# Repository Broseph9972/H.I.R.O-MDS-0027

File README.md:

# H.I.R.O-MDS-0027
a music video faithful mp3 player based on the H.I.R.O from good kid Music videos. built for Hack club fallout in about 2 weeks. My favorite Hardware project yet
---

I unironically listened to almost exclusively good kid while making this project.

---
## Why?
I've always loved good kid, and i was bored at night watching some of their music videos, and saw a scene of the H.I.R.O taken apart with a soldering iron,[^1] and realised, i could probably make that.
I cant explain how to use it yet, as i have not built it yet, but it should go something like select a song or playlist, and itll play said song or playlist. (duh)
This is my first project where i'm not very concerned about budget, as it isnt completely practical, it just needs to look as close as possible to the original. I did get rid of the arms and legs because it would make it annoying to use imho.

# Assembly

## Read through this before starting just for understanding.

  1. Solder Parts Onto the PCB. As there are many SMD Components and small capacitors, reflow soldering is recommended. Use long header pins for the screen DO NOT SOLDER THE SCREEN TO THE PCB YET.
  2. If any Through Hole parts poke into the case, like the speaker, use pliers or something to take them off. there should be indents in the case for them though.
  3. Place the PCB Onto the Main Casing. If it dosent fit, just sand the part until it does.
  4. Screw In the screen to the 4 square brackets on the main casing with M3x14 Screws.
  5. Solder the Screen Connector pins to the screen. (if gpio are short, im so sorry but i would just desolder and use jumper wires.)
  6. Plug in the battery to the JST Connector. Slide it wherever it fits, i reccomend under the screen. any lipo battery should work.
  7. (vid isnt accurate) Slide the buttons into place so that the lip dosent allow it to get pushed out.
  8. Place the Lid on Top, Turn the main casing over, and screw in 3 M3x14 Screws.
  9. (Optional) Paint it! it looks so much cooler Painted. I highly reccomend this.

### Assembly Video (its really bad)
https://github.com/user-attachments/assets/d8cce7da-2541-4a06-ba8f-5a0993665533

# Usage
The H.I.R.O has 3 inputs.
1. Button 1
2. Button 2
3. Clicky Knob

Spin the knob to cycle through the options on the screen. Click the knob to select.
Button 1 is for skipping to the next song. Hold to skip past 10s at a time in a specific song.
Button 2 is for rewinding. Click once to go to the last song. click twice to restart the song. Hold to go back 10s at a time in the song. 
# Setup
  1. Flash the Firmware for the MP3 Using arduino IDE or whichever ide you prefer
  2. Insert MicroSD Card With Music on it in Mp3 (or FLAC?) Format.
  3. Play your Music!

## Warning:
Theres a bug where the lid has a huge object inside it when 3d printing, just delete it in your slicer. i dunno why this happens.

# Bill of Materials

| Name | Qty | Reference(s) | Price (USD) | Comments | Link |
|------|-----|--------------|-------------|----------|------|
| Seeed XIAO ESP32-S3 Plus | 1 | U1 | $7.59 | Main MCU module. SMD footprint (castellated). Source direct from Seeed for genuine part. | [Link](https://www.seeedstudio.com/Seeed-Studio-XIAO-ESP32S3-Plus-p-6361.html) |
| PCM5102A DAC (TSSOP-20) | 1 | U2 | $1.11 | Bare IC from LCSC (C107671). I2S DAC driving the 3.5mm headphone jack. | [Link](https://www.lcsc.com/product-detail/C107671.html) |
| MAX98357A Class-D Amplifier (TQFN-16) | 1 | U3 | $2.00 | Bare TQFN-16 3x3mm IC — NOT a breakout module. Check LCSC / DigiKey / Mouser for current price. | [Link](https://octopart.com/max98357aete+t-maxim+integrated-33346832) |
| CVS-1708 Speaker | 1 | LS1 | $4.02 | 8Ω 200mW 1.2kHz–20kHz. Same Sky (formerly CUI). DigiKey. | [Link](https://www.digikey.com/en/products/detail/same-sky-formerly-cui-devices/CVS-1708/2791829) |
| Hirose DM3AT-SF-PEJM5 microSD Slot | 1 | J1 | $1.53 | Push-push with card detect. LCSC (C114218). | [Link](https://www.lcsc.com/product-detail/SD-Card-Connectors_HRS-Hirose-DM3AT-SF-PEJM5_C114218.html) |
| CUI SJ-3523-SMT-TR 3.5mm Audio Jack | 1 | J2 | $0.88 | Horizontal SMT stereo TRS jack. DigiKey. | [Link](https://www.digikey.com/en/products/detail/cui-devices/SJ-3523-SMT-TR/281297) |
| 1×8 Pin Header 2.54mm (through-hole) | 1 | J3 | $7.99 | Screen connector for Waveshare LCD. Must use long header pins (see assembly notes). | [Link](https://www.amazon.com/whiteeeen-Break-Away-Header-Straight-Connector/dp/B0B75RKMD2) |
| JST PH S2B-PH-K 2-pin Connector | 1 | J4 | $0.11 | Battery connector. 2.0mm pitch horizontal SMT. | [Link](https://www.digikey.com/en/products/detail/jst-sales-america-inc/S2B-PH-K-S/926626) |
| Omron B3U-3100P-B Side Push Button | 2 | S1 / S2 | $1.17 | SMD side-actuated tactile. DigiKey. ×2 units needed. | [Link](https://www.digikey.com/en/products/detail/omron-electronics-inc-emc-div/B3U-3100P-B/1811780) |
| EC11 Right-Angle Rotary Encoder (w/ switch) | 1 | SW1 | $4.07 | Push-switch + encoder. Right-angle EC11. | [Link](https://www.aliexpress.us/item/3256809185234399.html) |
| Capacitor 10µF 0603 | 4 | C1 / C4 / C5 / C6 | $0.01 | X5R or X7R ceramic decoupling. Order from LCSC. | [Link](https://www.lcsc.com/search?q=10uF+0603) |
| Capacitor 100nF 0603 | 2 | C2 / C3 | $0.01 | X7R ceramic decoupling. Order from LCSC. | [Link](https://www.lcsc.com/search?q=100nF+0603) |
| Resistor 1MΩ 0603 | 1 | R1 | $0.01 | 1% tolerance preferred. Order from LCSC. | [Link](https://www.lcsc.com/search?q=1M+0603+resistor) |
| Waveshare 2.4in LCD Module | 1 | — | $18.99 | 240×320 SPI (ILI9341). Connects to J3 header. Closest size match to original H.I.R.O screen. | [Link](https://www.amazon.com/Waveshare-2-4inch-Display-Resolution-Interface/dp/B08H24H7KX) |
| LiPo Battery 3.7V | 1 | — | $9.99 | Any single-cell LiPo with JST PH 2.0mm connector. Slides under screen in case. 500mAh+ recommended. | [Link](https://www.amazon.com/Battery-Rechargeable-Lithium-Polymer-Connector/dp/B07S84SBV3) |
| M3×14 Socket Head Cap Screws | 7 | — | $6.99 | 4× screen brackets + 3× lid. Stainless steel A2. | [Link](https://a.co/d/00dNH8NP) |
| 3D Printed Main Casing | 1 | — | $0.10 | Print from Cad/ directory. Sand if needed for PCB fit (see assembly notes). | [Link](https://github.com/Broseph9972/H.I.R.O-MDS-0027/tree/main/Cad) |
| 3D Printed Lid | 1 | — | $0.10 | Print from Cad/ directory. 3× M3×14 screw holes. | [Link](https://github.com/Broseph9972/H.I.R.O-MDS-0027/tree/main/Cad) |
| Custom PCB (H.I.R.O) | 1 | — | $7.50 | Fabricate from Pcb/ gerbers. JLCPCB / PCBWay / OSH Park. | [Link](https://github.com/Broseph9972/H.I.R.O-MDS-0027/tree/main/Pcb) |
| Paint (optional) | 1 | — | $0 | Spray paint or acrylic. | — |
| **TOTAL** | — | — | **$75.38** | Qty × unit price across all lines (screws/header counted as pack price; optional paint at $0). | — |

[^1]:From [Eastside](https://www.youtube.com/watch?v=-kVTMlbAywQ) [Wall](https://www.youtube.com/watch?v=HG8WEN3SKVk)[Mimis Delivery Service](https://www.youtube.com/watch?v=hYUvI5Njbbk)

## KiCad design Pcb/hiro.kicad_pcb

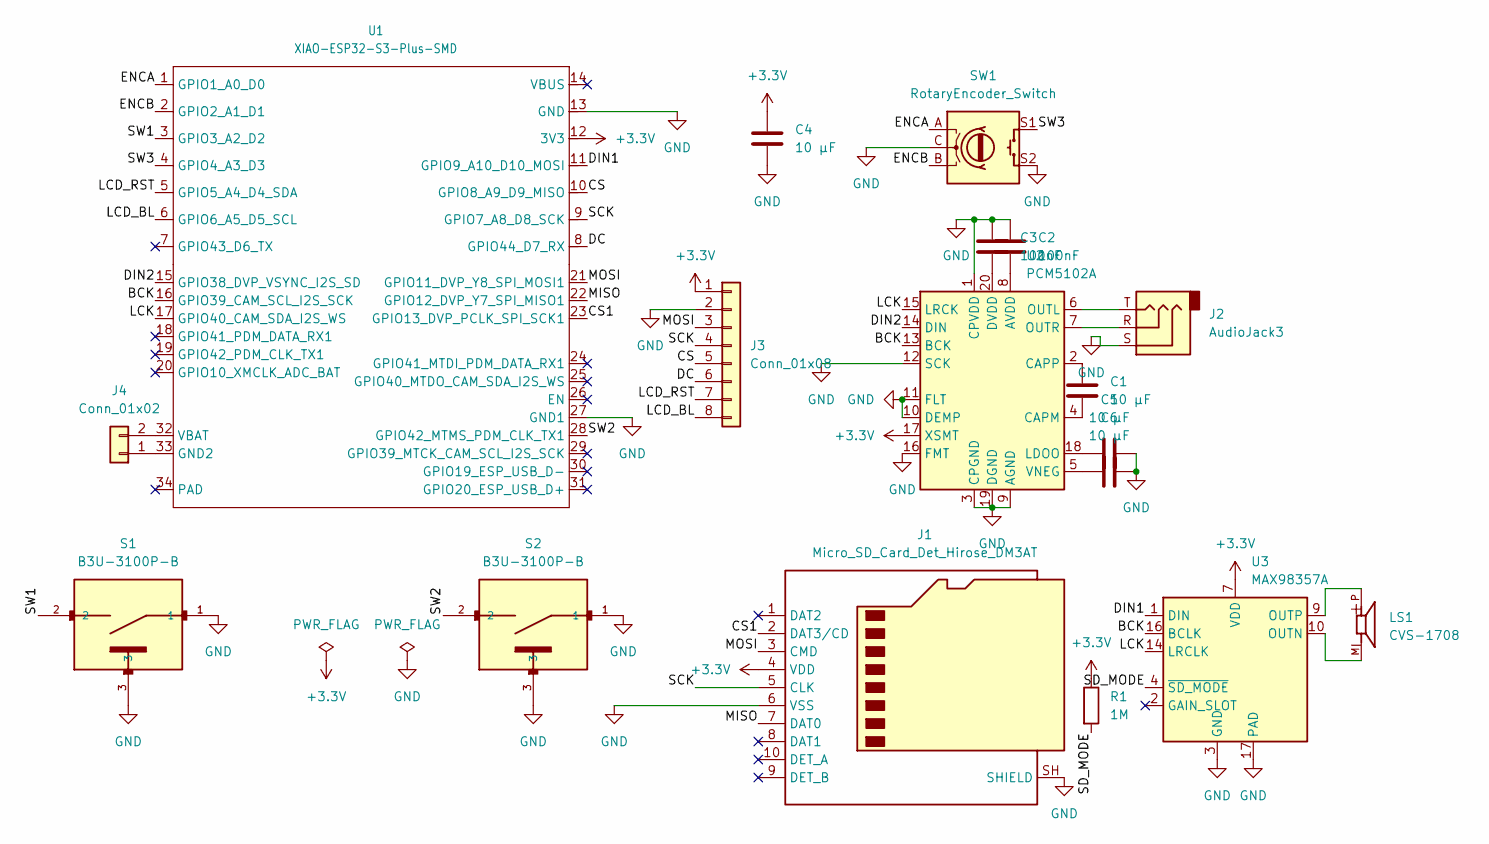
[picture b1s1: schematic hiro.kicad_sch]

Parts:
C1, C4, C5, C6: 10 µF; C_0603_1608Metric_Pad1.08x0.95mm_HandSolder
C2, C3: 100nF; C_0603_1608Metric_Pad1.08x0.95mm_HandSolder
J1: Micro_SD_Card_Det_Hirose_DM3AT; microSD_HC_Hirose_DM3AT-SF-PEJM5
J2: AudioJack3; Jack_3.5mm_CUI_SJ-3523-SMT_Horizontal
J3: Conn_01x08; PinHeader_1x08_P2.54mm_Vertical
J4: Conn_01x02; JST_PH_S2B-PH-K_1x02_P2.00mm_Horizontal
LS1: CVS-1708; SPKR_CVS-1708
R1: 1M; R_0603_1608Metric_Pad0.98x0.95mm_HandSolder
S1, S2: B3U-3100P-B; SW_SPST_B3U-3100P
SW1: RotaryEncoder_Switch; Right angle EC11 Rotary Encoder
U1: XIAO-ESP32-S3-Plus-SMD
U2: PCM5102A; TSSOP-20_4.4x6.5mm_P0.65mm
U3: MAX98357A; TQFN-16-1EP_3x3mm_P0.5mm_EP1.23x1.23mm

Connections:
+3.3V: C4.1, J1.4 (VDD), J3.1, R1.1, U1.12 (3V3), U2.17 (XSMT), U3.7 (VDD), U3.8 (VDD)
/BCK: U1.16 (GPIO39_CAM_SCL_I2S_SCK), U2.13 (BCK), U3.16 (BCLK)
/CS: J3.5, U1.10 (GPIO8_A9_D9_MISO)
/CS1: J1.2 (DAT3/CD), U1.23 (GPIO13_DVP_PCLK_SPI_SCK1)
/DC: J3.6, U1.8 (GPIO44_D7_RX)
/DIN1: U1.11 (GPIO9_A10_D10_MOSI), U3.1 (DIN)
/DIN2: U1.15 (GPIO38_DVP_VSYNC_I2S_SD), U2.14 (DIN)
/ENCA: SW1.A, U1.1 (GPIO1_A0_D0)
/ENCB: SW1.B, U1.2 (GPIO2_A1_D1)
/LCD_BL: J3.8, U1.6 (GPIO6_A5_D5_SCL)
/LCD_RST: J3.7, U1.5 (GPIO5_A4_D4_SDA)
/LCK: U1.17 (GPIO40_CAM_SDA_I2S_WS), U2.15 (LRCK), U3.14 (LRCLK)
/MISO: J1.7 (DAT0), U1.22 (GPIO12_DVP_Y7_SPI_MISO1)
/MOSI: J1.3 (CMD), J3.3, U1.21 (GPIO11_DVP_Y8_SPI_MOSI1)
/SCK: J1.5 (CLK), J3.4, U1.9 (GPIO7_A8_D8_SCK)
/SD_MODE: R1.2, U3.4 (~SD_MODE)
/SW1: S1.2, U1.3 (GPIO3_A2_D2)
/SW2: S2.2, U1.28 (GPIO42_MTMS_PDM_CLK_TX1)
/SW3: SW1.S1, U1.4 (GPIO4_A3_D3)
GND: C2.1, C3.1, C4.2, C5.2, C6.2, J1.6 (VSS), J1.SH (SHIELD), J2.S, J3.2, S1.1, S1.3, S2.1, S2.3, SW1.C, SW1.S2, U1.13 (GND), U1.27 (GND1), U2.1 (CPVDD), U2.3 (CPGND), U2.9 (AGND), U2.10 (DEMP), U2.11 (FLT), U2.12 (SCK), U2.16 (FMT), U2.19 (DGND), U3.3 (GND), U3.11 (GND), U3.15 (GND), U3.17 (PAD)
unnamed: J4.1, U1.33 (GND2)
unnamed: J4.2, U1.32 (VBAT)
unnamed: C2.2, U2.8 (AVDD)
unnamed: C1.2, U2.4 (CAPM)
unnamed: C1.1, U2.2 (CAPP)
unnamed: C3.2, U2.20 (DVDD)
unnamed: C5.1, U2.18 (LDOO)
unnamed: J2.T, U2.6 (OUTL)
unnamed: J2.R, U2.7 (OUTR)
unnamed: C6.1, U2.5 (VNEG)
unnamed: LS1.M, U3.10 (OUTN)
unnamed: LS1.P, U3.9 (OUTP)

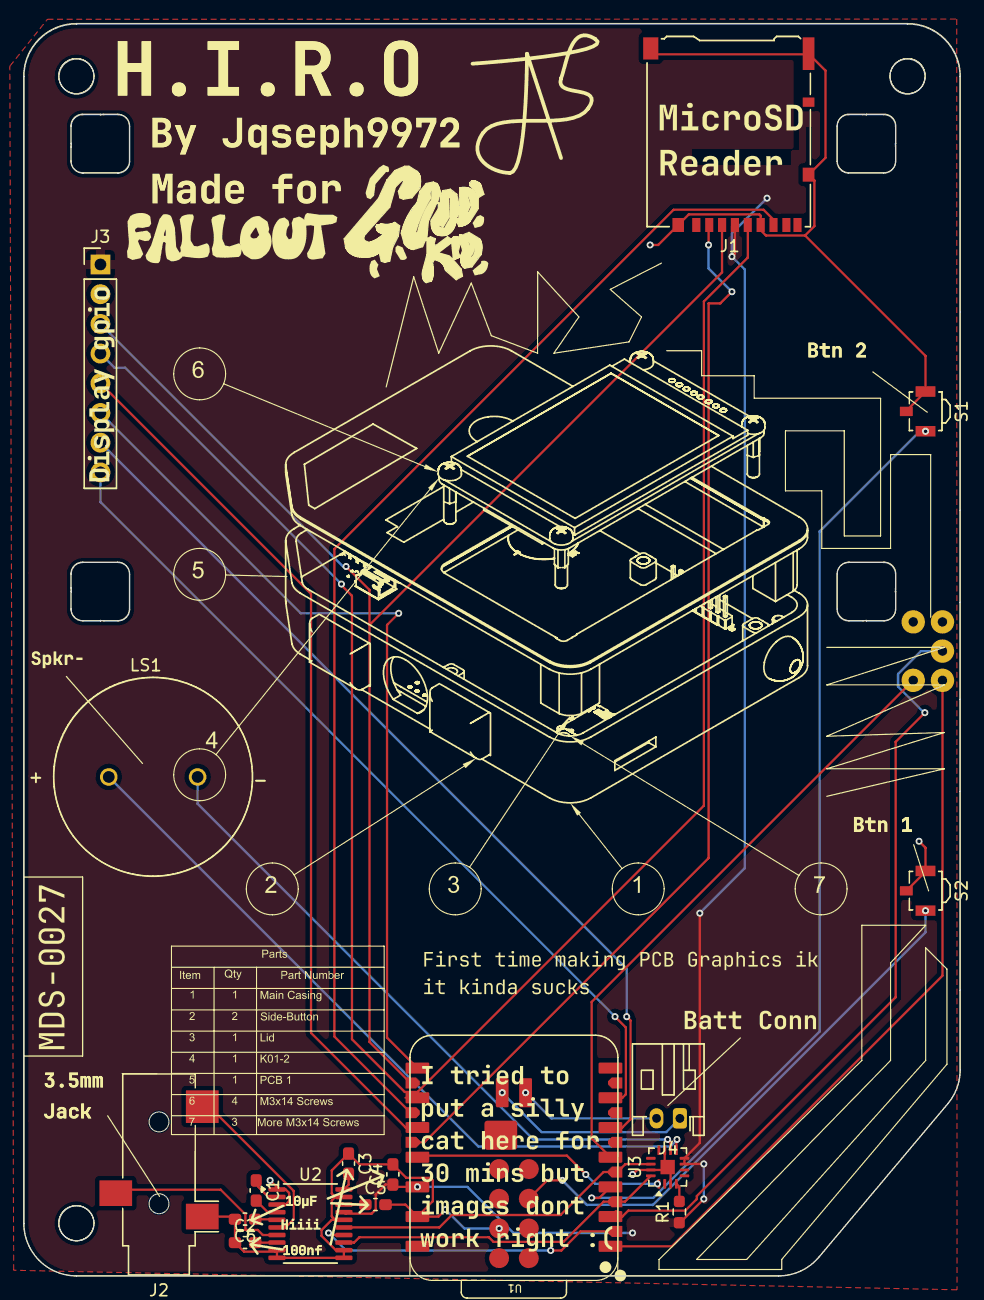
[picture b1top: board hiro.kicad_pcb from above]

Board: 2 copper layers, 80.1 x 107.1 mm, 18 parts (0 on the bottom side), 32 nets.

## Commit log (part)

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2026-06-05 peeseebi
2026-06-06 schematic parts
    added a really nice microsd card slot, an esp32-s3, and an audio jack.
2026-06-06 sooooooooooooooo much work
2026-06-07 THE OUTLINE WORKS YAYYY
2026-06-07 Some stuff
    it is def broken rn will fix laterrr
2026-06-07 New wiring cause botato is awesome
2026-06-07 got a sideway switch working correctly.
2026-06-08 Speaker + Speaker amp and 3d model
2026-06-09 Some stuffs
2026-06-09 New Speaker, some new cad, other stuff, renders, etc
2026-06-10 asdsad
2026-06-11 Placed The screen connector in (almost) the right spot
2026-06-12 Lots of wiring
2026-06-12 Final PCB (rev1)
2026-06-12 Assembly
2026-06-15 moved speaker
    It now lines up with the like left square thingy in the art.
2026-06-15 step file
2026-06-15 Organized
2026-06-15 Some changes i forget
2026-06-15 FINAL PCB FINAL PCB FINAL PCB
2026-06-15 Code
2026-06-15 small readme fix
2026-06-16 test
2026-06-17 Bom table in readme
2026-06-17 Added zine
2026-06-17 Added pic of zine
2026-06-17 New zine
2026-06-17 Gerbers for pcb
2026-06-17 better readme
2026-06-17 didnt add csv cause readme brooo
2026-06-17 CAD FILE EXPORT
2026-06-17 renamed
2026-06-17 gerbers and bom
2026-06-17 pcb price
2026-06-20 Made a bunch of sprites for the screen
2026-06-20 added totals to bom and readme bom
2026-06-22 new cad
2026-06-23 Made cad work
    Fixed an issue where the screw holes overlapped with the other screw holes so the case wont assemble.
2026-06-23 also this
